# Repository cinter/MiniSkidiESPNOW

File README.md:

# MiniSkidiESPNOW
Branch of ProfBoots MiniSkidi code to support a custom controller with control via ESPNOW wifi. The code uploaded here will be working code, so don't worry if there are few commits. I use this repo as a backup of known good states. I am not a coder, this is all generated with Gemini and checked by Codex.

## 3D files
The original controller design can be found on OnShape [here](https://cad.onshape.com/documents/6bafb625ffbc5bb075599570/w/3596931d871cc26ccb4a224e/e/206217da13ada2750408ef04).

Printable files are [here](https://www.printables.com/model/1694698-miniskidi-controller), and I'll try to keep a list of components below.

## Components
Custom circuit board: KiCad files can be downloaded from Controller_V2 here. Ordered from JLCPCB, but PCBWay and others work too.  
Joystick: [Analog 2-axis Thumb Joystick with Select Button + Breakout Board](https://thepihut.com/products/adafruit-analog-2-axis-thumb-joystick-with-select-button-breakout-board)  
ESP32-C3 XIAO dev board: [Seeed XIAO ESP32C3](https://thepihut.com/products/seeed-xiao-esp32c3?variant=53975115694465)  
Battery: [3.7V 600mAh Battery](https://www.amazon.co.uk/dp/B0DB1X3RK7)  
Toggle switch: [5mm	toggle](https://www.amazon.co.uk/dp/B088R3GYWP)  
Tacctile buttons: [PCB buttons, these or similar](https://www.mouser.co.uk/ProductDetail/Same-Sky/TS04-66-85-BK-160-SMT-TR?qs=VJzv269c%252BPaHwNn0xD14PA%3D%3D)  
LED: [Neopixel LED](https://thepihut.com/products/neopixel-5050-rgb-led-with-integrated-driver-chip-10-pack)  
Cap for NeoPixel: [0.1uF Capacitor](https://uk.farnell.com/vishay/k104k15x7rf5tl2/cap-0-1-f-50v-10-x7r/dp/2860097)  
Light pipe:	[3mm, 1mm length](https://uk.farnell.com/mentor/1282-1405/light-pipe-1pipe-11mm-l-panel/dp/4562818)

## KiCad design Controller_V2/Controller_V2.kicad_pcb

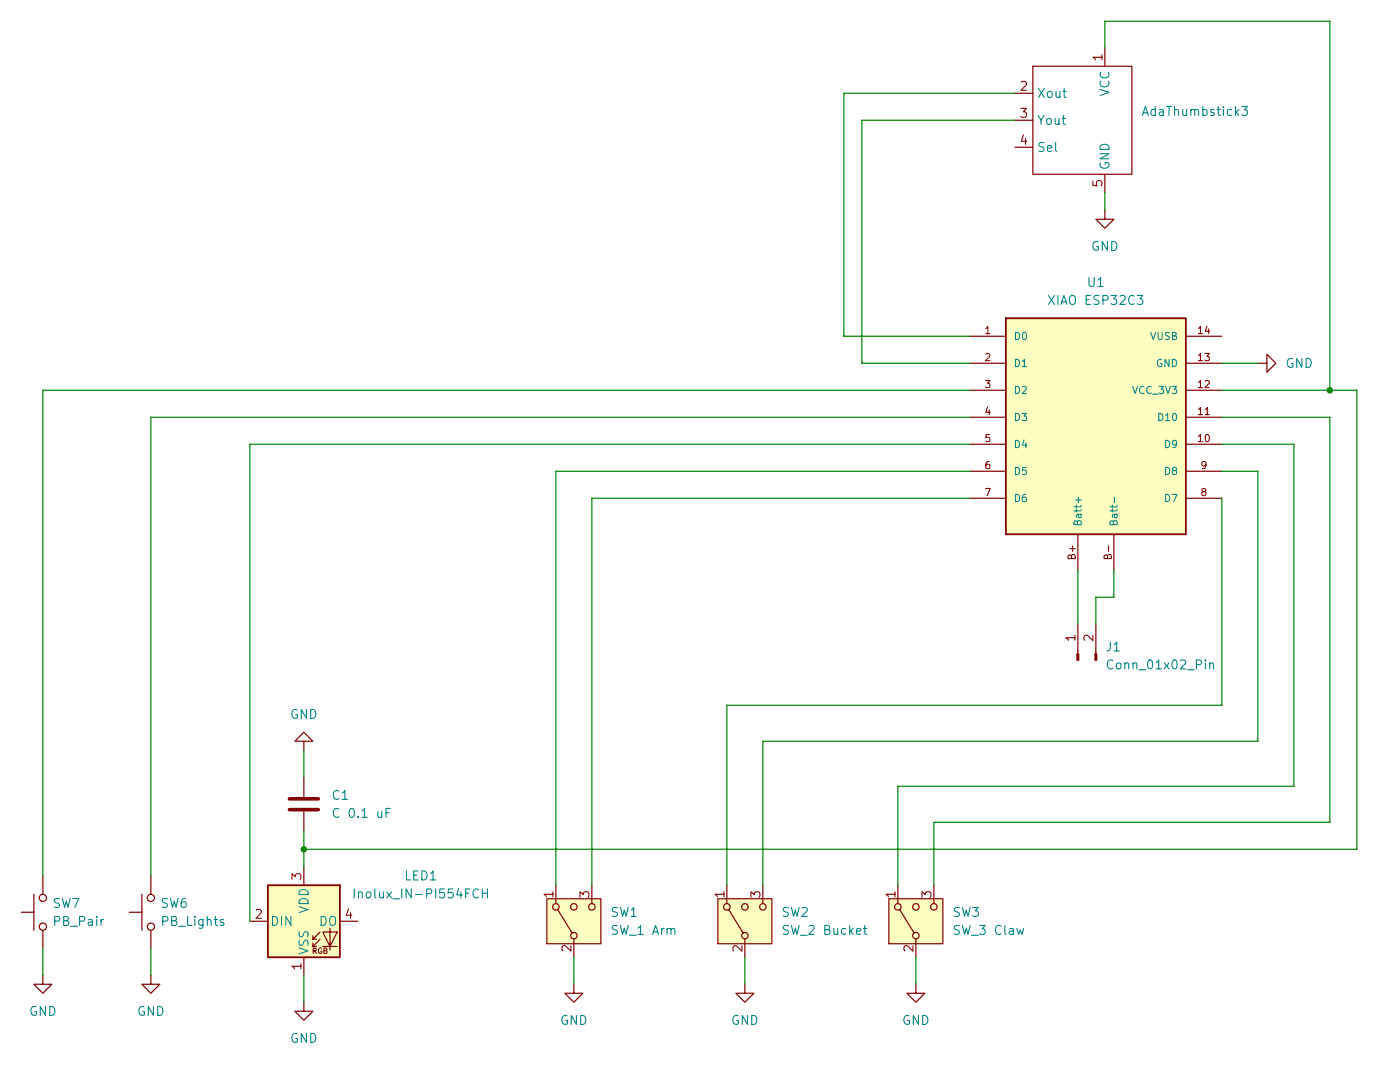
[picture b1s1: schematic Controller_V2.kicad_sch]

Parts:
AdaThumbstick3: PinSocket_1x05_P2.54mm_Vertical
C1: C 0.1 uF; C_Disc_D4.3mm_W1.9mm_P5.00mm
J1: Conn_01x02_Pin; JST_PH_S2B-PH-K_1x02_P2.00mm_Horizontal
LED1: Inolux_IN-PI554FCH; LED_Inolux_IN-PI554FCH_PLCC4_5.0x5.0mm_P3.2mm
SW1: SW_1 Arm; Toggle switch
SW2: SW_2 Bucket; Toggle switch
SW3: SW_3 Claw; Toggle switch
SW6: PB_Lights; SW_PUSH_6mm_H5mm
SW7: PB_Pair; SW_PUSH_6mm_H5mm
U1: XIAO ESP32C3

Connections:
GND: AdaThumbstick3.5 (GND), C1.1, LED1.1 (VSS), SW1.2 (3), SW2.2 (3), SW3.2 (3), SW6.1, SW7.1, U1.13 (GND)
unnamed: AdaThumbstick3.1 (VCC), C1.2, LED1.3 (VDD), U1.12 (VCC_3V3)
unnamed: AdaThumbstick3.2 (Xout), U1.1 (D0)
unnamed: AdaThumbstick3.3 (Yout), U1.2 (D1)
unnamed: J1.1, U1.B+ (Batt+)
unnamed: J1.2, U1.B- (Batt-)
unnamed: LED1.2 (DIN), U1.5 (D4)
unnamed: SW1.3 (4), U1.7 (D6)
unnamed: SW2.3 (4), U1.9 (D8)
unnamed: SW3.3 (4), U1.11 (D10)
unnamed: SW7.2, U1.3 (D2)
unnamed: SW6.2, U1.4 (D3)
unnamed: SW1.1, U1.6 (D5)
unnamed: SW2.1, U1.8 (D7)
unnamed: SW3.1, U1.10 (D9)

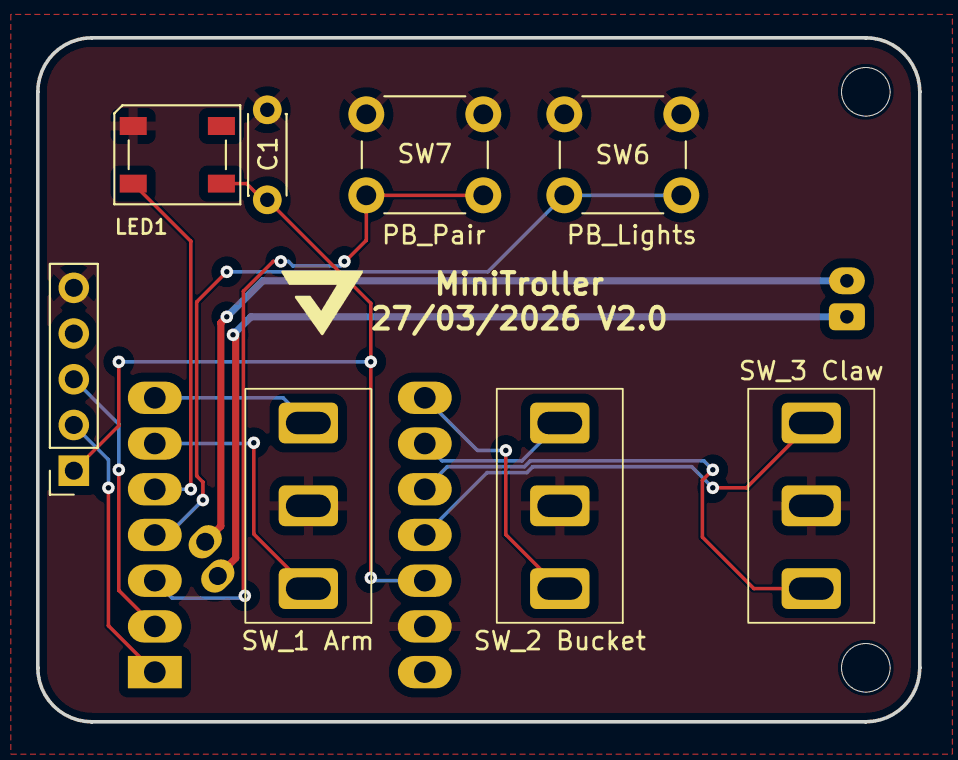
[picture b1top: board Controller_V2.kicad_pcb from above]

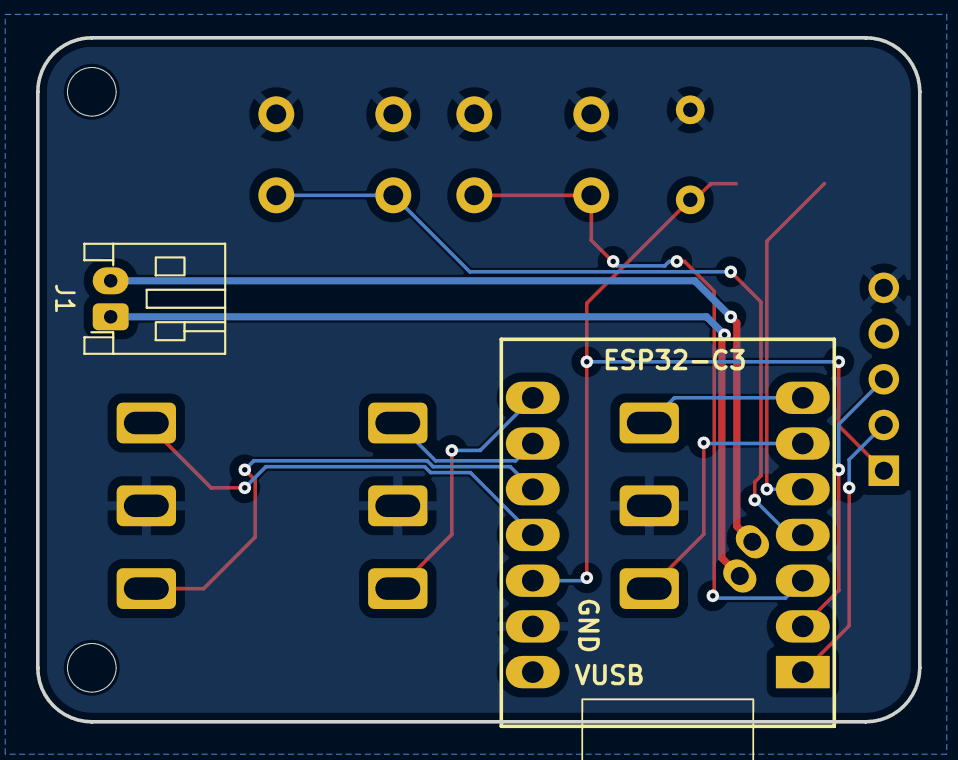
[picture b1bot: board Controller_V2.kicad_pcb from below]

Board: 2 copper layers, 49.0 x 38.0 mm, 10 parts (2 on the bottom side), 15 nets.

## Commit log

2026-04-12 Initial upload
2026-04-19 Handle low battery better
    Added crash counter to handle brownout resets and prevent repeated crashes.
    Reduced LED brightness significantly.
2026-04-19 Enhance README with detailed project information
    Expanded project description and added links to original design and STL files.
2026-04-19 Update motor PWM configuration for left motor
2026-04-22 Enhance README with 3D files and components details
    Updated README to include additional sections for 3D files and components with links.
2026-04-22 Update README formatting and section headings
2026-05-05 Enable debug logging and improve state management
